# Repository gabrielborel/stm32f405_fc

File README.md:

STM32F405 MCU based flight controller PCB design using Kicad and firmware design project.

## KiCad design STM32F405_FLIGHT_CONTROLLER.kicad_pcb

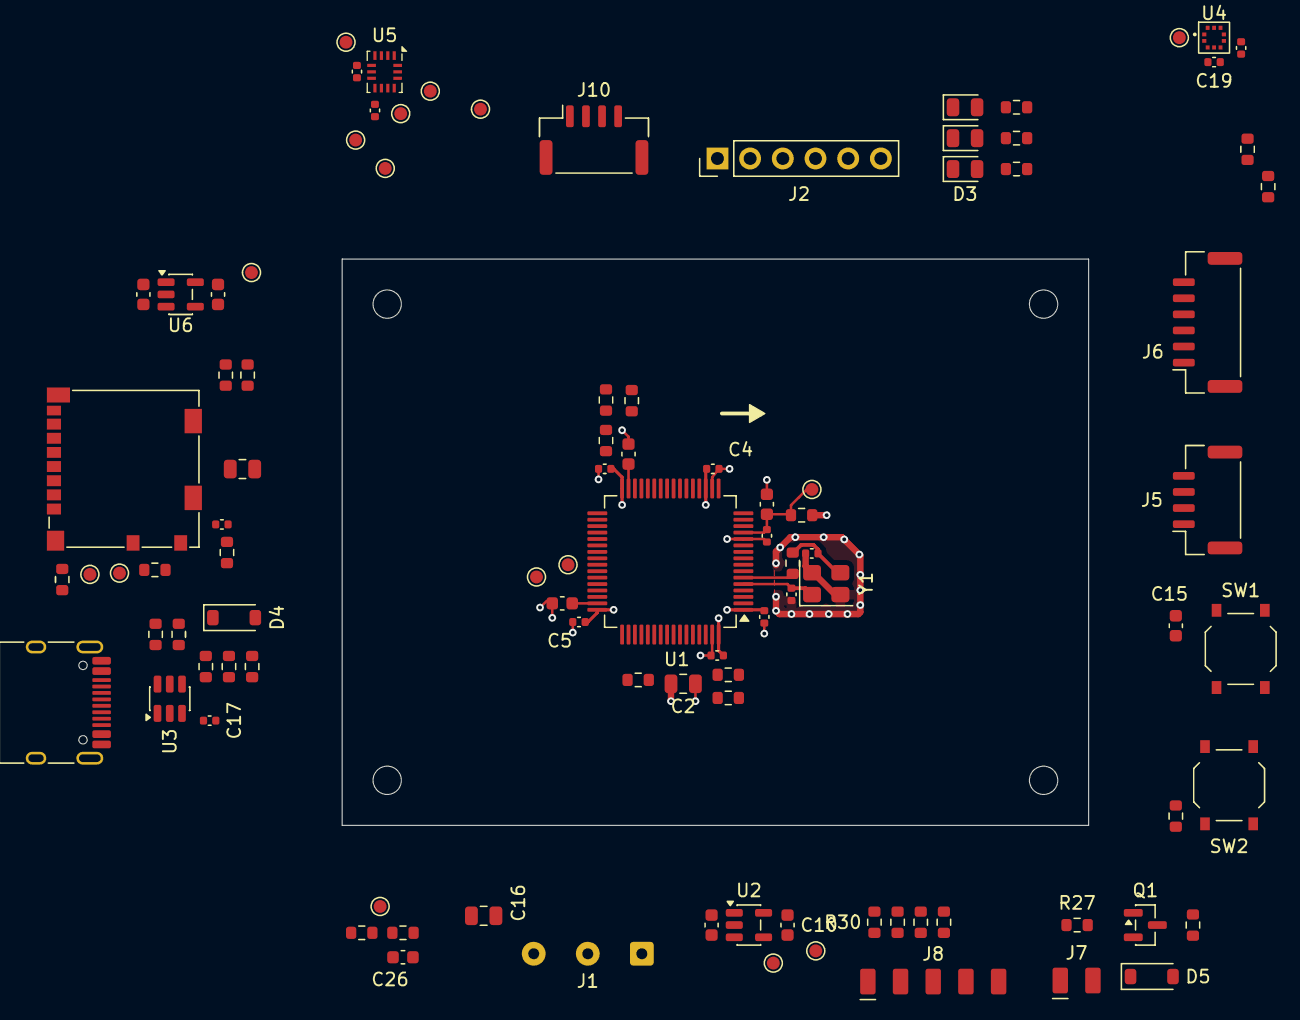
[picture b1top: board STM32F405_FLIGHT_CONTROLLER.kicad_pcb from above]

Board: 4 copper layers, 58.0 x 44.0 mm, 102 parts (0 on the bottom side), 64 nets.

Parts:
C1, C3, C4, C5, C6, C8, C17, C18, C19, C20, C21, C25: 100nF; C_0402_1005Metric
C2: 4u7; C_0805_2012Metric
C7, C9, C10, C22, C23: 1u; C_0603_1608Metric
C11, C12: 2u2; C_0603_1608Metric
C13, C14: 15pF; C_0402_1005Metric
C15, C26: 100nF; C_0603_1608Metric
C16, C24: 10uF,25V; C_0805_2012Metric
D1: KT-0805G; LED_0805_2012Metric
D2: KT-0805Y; LED_0805_2012Metric
D3: NCD0805R1; LED_0805_2012Metric
D4, D5: B5819W SL; D_SOD-123
H1, H2, H3, H4: MountingHole; MountingHole_2.2mm_M2
J1: PDB pads; SolderWire-0.25sqmm_1x03_P4.2mm_D0.65mm_OD1.7mm
J2: Debugger connector; PinHeader_1x06_P2.54mm_Vertical
J3: USB_C Conn 16P; USB_C_Receptacle_HRO_TYPE-C-31-M-12
J4: Micro SD Card; microSD_HC_Molex_104031-0811
J5: ELRS Conn; JST_GH_SM04B-GHS-TB_1x04-1MP_P1.25mm_Horizontal
J6: GPS conn; JST_GH_SM06B-GHS-TB_1x06-1MP_P1.25mm_Horizontal
J7: Buzzer Pads; SolderPads_1x02_P2.54mm
J8: ESC Motors Pad; SolderPads_1x05_P2.54mm
J10: UART4 conn; JST_GH_SM04B-GHS-TB_1x04-1MP_P1.25mm_Horizontal
Q1: AO3400A; SOT-23
R1, R34: 0R; R_0603_1608Metric
R2: 100k; R_0603_1608Metric
R3, R4, R12, R16, R19, R20, R21, R22, R23, R29, R30, R31, R32, R33: 10k; R_0603_1608Metric
R5, R6: 470R; R_0603_1608Metric
R7: 2.2k; R_0603_1608Metric
R8, R9: 5K1; R_0603_1608Metric
R10: 33k; R_0603_1608Metric
R11: 82k; R_0603_1608Metric
R13, R14: 4k7; R_0603_1608Metric
R17, R24, R25, R26, R28: 220R; R_0603_1608Metric
R27: 1k; R_0603_1608Metric
SW1: Reset Button; SW_Push_1P1T_XKB_TS-1187A
SW2: Boot Sel Button; SW_Push_1P1T_XKB_TS-1187A
TP1: MCO1; TestPoint_Pad_D1.0mm
TP2, TP5, TP7: GND; TestPoint_Pad_D1.0mm
TP3: VBAT_SENSE; TestPoint_Pad_D1.0mm
TP4: VDDA; TestPoint_Pad_D1.0mm
TP6: +3V3; TestPoint_Pad_D1.0mm
TP8: MISO; TestPoint_Pad_D1.0mm
TP9: INT1; TestPoint_Pad_D1.0mm
TP10: MOSI; TestPoint_Pad_D1.0mm
TP11: CS; TestPoint_Pad_D1.0mm
TP12: SCK; TestPoint_Pad_D1.0mm
TP13: +3V3_SD; TestPoint_Pad_D1.0mm
TP14: SD_CMD; TestPoint_Pad_D1.0mm
TP15: SD_CK; TestPoint_Pad_D1.0mm
TP16: BMP_INT; TestPoint_Pad_D1.0mm
U1: STM32F405RGT6; LQFP-64_10x10mm_P0.5mm
U2, U6: AP2112K-3.3; SOT-23-5
U3: USBLC6-2SC6; SOT-23-6
U4: BMP581; LGA-10_L2.0-W2.0-P0.50-TL_BMP581
U5: BMI270; Bosch_LGA-14_3x2.5mm_P0.5mm
Y1: X32258MOB4SI - 150Ω 8MHz; Crystal_SMD_3225-4Pin_3.2x2.5mm

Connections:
+3.3VA: C7.1, C8.1, R34.2, TP4.1 (1_1), U1.13 (VDDA)
+3V3: C1.1, C2.1, C3.1, C4.1, C5.1, C6.1, C10.1, C18.2, C19.1, C20.2, C21.2, J2.1, R13.2, R14.1, R34.1, SW2.1, TP6.1 (1_1), U1.1 (VBAT), U1.19 (VDD), U1.32 (VDD), U1.48 (VDD), U1.64 (VDD), U2.5 (VOUT), U4.1 (VDDIO), U4.6 (CSB), U4.10 (VDD), U5.5 (VDDIO), U5.8 (VDD)
+3V3_SD: C23.1, C24.1, C25.1, J4.4 (VDD), R19.1, R20.1, R21.1, R22.1, R23.1, TP13.1 (1_1), U6.5 (VOUT)
+5V: C9.1, C16.2, C22.1, D1.2 (A), D2.2 (A), D3.2 (A), D4.1 (K), D5.1 (K), J1.3, J5.2, J6.2, J7.1, J10.2, R27.1, U2.1 (VIN), U2.3 (EN), U6.1 (VIN), U6.3 (EN)
/Buzzer/BZ_NEG: D5.2 (A), J7.2, Q1.3 (D), R27.2
/Motors/M1_OUT: J8.1, R17.2, R30.2
/Motors/M2_OUT: J8.2, R24.2, R31.2
/Motors/M3_OUT: J8.3, R25.2, R32.2
/Motors/M4_OUT: J8.4, R26.2, R33.2
/Power/+VBAT: J1.1, R2.1
/USB/USB_CONN_D+: J3.A6 (D+), J3.B6 (D+), U3.1 (I/O1)
/USB/USB_CONN_D-: J3.A7 (D-), J3.B7 (D-), U3.3 (I/O2)
/USB/VBUS_RAW: C17.2, D4.2 (A), J3.A4 (VBUS), J3.A9 (VBUS), J3.B4 (VBUS), J3.B9 (VBUS), R10.1, R12.1, U3.5 (VBUS)
BMP_INT: TP16.1 (1_1), U1.3 (PC14), U4.7 (INT)
BOOT0: R4.1, SW2.2, U1.60 (BOOT0)
BOOT1: R16.1, U1.28 (PB2)
BUZZER: R28.1, U1.58 (PB6)
ELRS_RX: J5.4, U1.30 (PB11)
ELRS_TX: J5.3, U1.29 (PB10)
GND: C1.2, C2.2, C3.2, C4.2, C5.2, C6.2, C7.2, C8.2, C9.2, C10.2, C11.2, C12.2, C13.2, C14.2, C15.2, C16.1, C17.1, C18.1, C19.2, C20.1, C21.1, C22.2, C23.2, C24.2, C25.2, C26.2, J1.2, J2.3, J3.A1 (GND), J3.A12 (GND), J3.B1 (GND), J3.B12 (GND), J3.SH (SHIELD), J4.6 (VSS), J4.9 (DET_B), J4.SH (SHIELD), J5.1, J6.1, J8.5, J10.1, Q1.2 (S), R3.2, R4.2, R8.2, R9.2, R11.2, R12.2, R16.2, R29.1, R30.1, R31.1, R32.1, R33.1, SW1.1, TP2.1 (1_1), TP5.1 (1_1), TP7.1 (1_1), U1.12 (VSSA), U1.18 (VSS), U1.63 (VSS), U2.2 (GND), U3.2 (GND), U4.3 (VSS), U4.5 (SDO), U4.8 (VSS), U4.9 (VSS), U5.6 (GNDIO), U5.7 (GND), U6.2 (GND), Y1.2 (G), Y1.4 (G)
GPS_RX: J6.4, U1.38 (PC7)
GPS_TX: J6.3, U1.37 (PC6)
I2C1_SCL: J6.5, R13.1, U1.61 (PB8), U4.2 (SCK)
I2C1_SDA: J6.6, R14.2, U1.62 (PB9), U4.4 (SDI)
IMU_INT1: TP9.1 (1_1), U1.17 (PA3), U5.4 (INT1)
LED_GREEN: R7.2, U1.24 (PC4)
LED_RED: R5.2, U1.9 (PC1)
LED_YELLOW: R6.2, U1.25 (PC5)
MOTOR1: R17.1, U1.56 (PB4)
MOTOR2: R24.1, U1.57 (PB5)
MOTOR3: R25.1, U1.26 (PB0)
MOTOR4: R26.1, U1.27 (PB1)
NRST: C15.1, J2.5, SW1.2, U1.7 (NRST)
unnamed: C14.1, R1.2, Y1.3
unnamed: D1.1 (K), R7.1
unnamed: D2.1 (K), R6.1
unnamed: D3.1 (K), R5.1
unnamed: J3.A5 (CC1), R8.1
unnamed: J3.B5 (CC2), R9.1
unnamed: Q1.1 (G), R28.2, R29.2
unnamed: TP1.1 (1_1), U1.41 (PA8)
unnamed: C11.1, U1.31 (VCAP_1)
unnamed: C12.1, U1.47 (VCAP_2)
OSC_IN: C13.1, U1.5 (PH0), Y1.1
OSC_OUT: R1.1, U1.6 (PH1)
SDIO_CK: J4.5 (CLK), TP15.1 (1_1), U1.53 (PC12)
SDIO_CMD: J4.3 (CMD), R21.2, TP14.1 (1_1), U1.54 (PD2)
SDIO_D0: J4.7 (DAT0), R20.2, U1.39 (PC8)
SDIO_D1: J4.8 (DAT1), R19.2, U1.40 (PC9)
SDIO_D2: J4.1 (DAT2), R23.2, U1.51 (PC10)
SDIO_D3: J4.2 (DAT3/CD), R22.2, U1.52 (PC11)
SPI1_IMU_CS: TP11.1 (1_1), U1.20 (PA4), U5.12 (CSB)
SPI1_MISO: TP8.1 (1_1), U1.22 (PA6), U5.1 (SDO)
SPI1_MOSI: TP10.1 (1_1), U1.23 (PA7), U5.14 (SDX)
SPI1_SCK: TP12.1 (1_1), U1.21 (PA5), U5.13 (SCX)
SWCLK: J2.2, U1.49 (PA14)
SWDIO: J2.4, U1.46 (PA13)
SWO: J2.6, U1.55 (PB3)
UART4_RX: J10.4, U1.15 (PA1)
UART4_TX: J10.3, U1.14 (PA0)
USB_D+: U1.45 (PA12), U3.6 (I/O1)
USB_D-: U1.44 (PA11), U3.4 (I/O2)
VBAT_SENSE: C26.1, R2.2, R3.1, TP3.1 (1_1), U1.8 (PC0)
VBUS_DET: R10.2, R11.1, U1.42 (PA9)

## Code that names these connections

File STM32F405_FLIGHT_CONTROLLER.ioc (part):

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Mcu.Name=STM32F405RGTx
Mcu.Package=LQFP64
Mcu.UserName=STM32F405RGTx
PA11.Mode=Device_Only
PA11.Signal=USB_OTG_FS_DM
PA12.Mode=Device_Only
PA12.Signal=USB_OTG_FS_DP
PA13.Mode=Serial_Wire
PA13.Signal=SYS_JTMS-SWDIO
PA14.Mode=Serial_Wire
PA14.Signal=SYS_JTCK-SWCLK
PA3.GPIOParameters=GPIO_Label,GPIO_ModeDefaultEXTI
PA3.GPIO_Label=SPI1_IMU_INT
PA3.GPIO_ModeDefaultEXTI=GPIO_MODE_IT_FALLING
PA3.Signal=GPXTI3
PA4.GPIOParameters=PinState,GPIO_PuPd,GPIO_Label
PA4.GPIO_Label=SP1_IMU_CS
PA4.GPIO_PuPd=GPIO_NOPULL
PA4.PinState=GPIO_PIN_SET
PA4.Signal=GPIO_Output
PA5.GPIOParameters=GPIO_Speed
PA5.GPIO_Speed=GPIO_SPEED_FREQ_MEDIUM
PA5.Mode=Full_Duplex_Master
PA5.Signal=SPI1_SCK
PA6.Mode=Full_Duplex_Master
PA6.Signal=SPI1_MISO
PA7.Mode=Full_Duplex_Master
PA7.Signal=SPI1_MOSI
PA9.GPIOParameters=GPIO_Label
PA9.GPIO_Label=VBUS_DET
PA9.Signal=GPIO_Input
PB2.GPIOParameters=GPIO_Label
PB2.GPIO_Label=BOOT1_RESERVED
PB2.Signal=GPIO_Input
PB8.Mode=I2C
PB8.Signal=I2C1_SCL
PB9.Mode=I2C
PB9.Signal=I2C1_SDA
PC0.GPIOParameters=GPIO_Label
PC0.GPIO_Label=VBAT_SENSE
PC0.Signal=ADCx_IN10
PC1.GPIOParameters=PinState,GPIO_Label,GPIO_ModeDefaultOutputPP
PC1.GPIO_Label=LED_RED
PC1.GPIO_ModeDefaultOutputPP=GPIO_MODE_OUTPUT_PP
PC1.PinState=GPIO_PIN_SET
PC1.Signal=GPIO_Output
PC10.Mode=SD_4_bits_Wide_bus
PC10.Signal=SDIO_D2
PC11.Mode=SD_4_bits_Wide_bus
PC11.Signal=SDIO_D3
PC12.Mode=SD_4_bits_Wide_bus
PC12.Signal=SDIO_CK
PC4.GPIOParameters=PinState,GPIO_Label,GPIO_ModeDefaultOutputPP
PC4.GPIO_Label=LED_GREEN
PC4.GPIO_ModeDefaultOutputPP=GPIO_MODE_OUTPUT_PP
PC4.PinState=GPIO_PIN_SET
PC4.Signal=GPIO_Output
PC5.GPIOParameters=PinState,GPIO_Label,GPIO_ModeDefaultOutputPP
PC5.GPIO_Label=LED_BLUE
PC5.GPIO_ModeDefaultOutputPP=GPIO_MODE_OUTPUT_PP
PC5.PinState=GPIO_PIN_SET
PC5.Signal=GPIO_Output
PC8.Mode=SD_4_bits_Wide_bus
PC8.Signal=SDIO_D0
PC9.Mode=SD_4_bits_Wide_bus
PC9.Signal=SDIO_D1
PD2.Mode=SD_4_bits_Wide_bus
PD2.Signal=SDIO_CMD
PH0-OSC_IN.Mode=HSE-External-Oscillator
PH0-OSC_IN.Signal=RCC_OSC_IN
PH1-OSC_OUT.Mode=HSE-External-Oscillator
PH1-OSC_OUT.Signal=RCC_OSC_OUT
RCC.HSE_VALUE=8000000
RCC.SYSCLKFreq_VALUE=168000000
RCC.SYSCLKSource=RCC_SYSCLKSOURCE_PLLCLK
board=custom
